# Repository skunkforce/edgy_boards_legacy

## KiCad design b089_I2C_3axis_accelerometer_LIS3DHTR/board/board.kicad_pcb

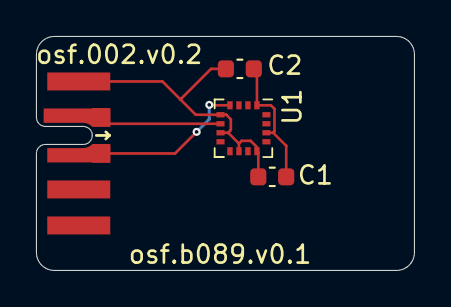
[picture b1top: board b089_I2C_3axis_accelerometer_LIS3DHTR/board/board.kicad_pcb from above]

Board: 2 copper layers, 21.0 x 13.0 mm, 4 parts (0 on the bottom side), 4 nets.

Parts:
C1: 100nF; C_0603_1608Metric
C2: 10uF; C_0603_1608Metric
J1: 001_I2C; on_edge_2x05_device
U1: LIS3DHTR; LGA-16_3x3mm_P0.5mm

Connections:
/sensor/3.3V: C1.2, C2.2, U1.1 (VDD_IO), U1.14 (VDD)
/sensor/SCL: J1.3 (SCL), U1.4 (SCL/SPC)
/sensor/SDA: J1.2 (SDA), U1.6 (SDA/SDI/SDO)
GND: C1.1, C2.1, J1.1 (GND), U1.5 (GND), U1.7 (SDO/SA0), U1.10 (RES), U1.12 (GND)

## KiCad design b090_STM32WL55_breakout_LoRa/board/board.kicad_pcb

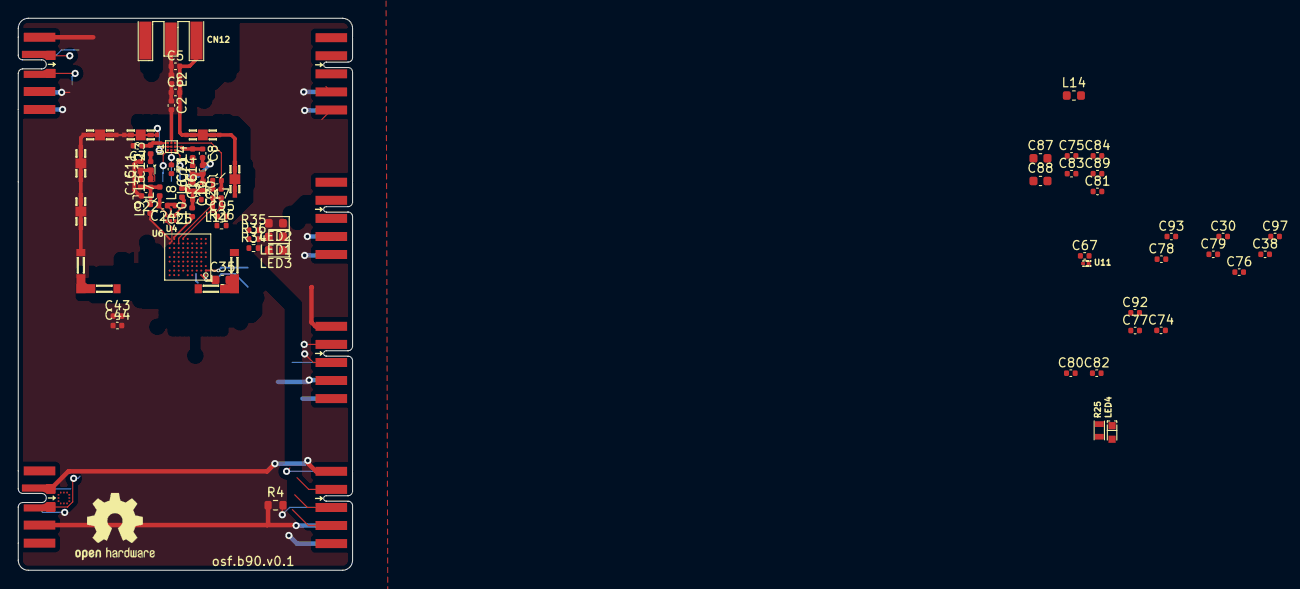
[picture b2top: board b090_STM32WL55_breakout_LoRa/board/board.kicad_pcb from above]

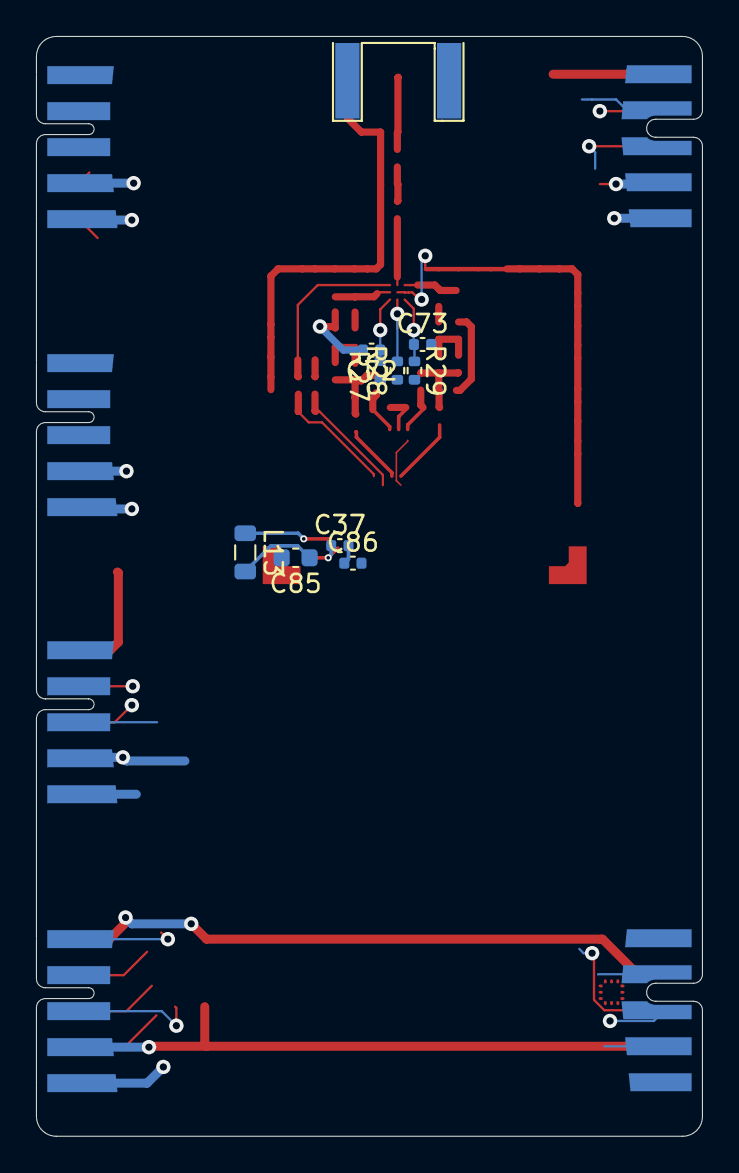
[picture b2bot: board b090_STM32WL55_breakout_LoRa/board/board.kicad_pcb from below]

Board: 4 copper layers, 37.0 x 61.1 mm, 93 parts (9 on the bottom side), 9 nets.

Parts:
C2, C5, C6, C8, C13, C14, C16, C19, C20, C21, C24, C25, C30, C37, C38, C43, C44, C71, C72, C73, C74, C75, C76, C77, C78, C79, C80, C81, C82, C83, C84, C86, C89: C_0402_1005Metric
C7, C11, C12, C15, C17, C22, C92, C93, C95, C97: Capacitor; C_0402_1005Metric
C35, C85, C87, C88: C_0603_1608Metric
C67: C_0402_1005Metric
CN12: CON_SAMTEC_SMA-J-P-X-ST-EM1
J1: DebugEdge_02x05; debug_edge_2x05_device
J2: SPI_2x3; on_edge_2x05_host
J4: UART_2x2; on_edge_2x05_device
J7: I2C_2x2; on_edge_2x05_host
J8: UART_2x2; on_edge_2x05_host
J9: ADC_2x3; on_edge_2x05_host
L2, L4, L8, L9, L10: L_0402_1005Metric
L3, L5, L6, L7, L11: Inductor; L_0402_1005Metric
L13: L_0805_2012Metric
L14: L_0603_1608Metric
LED1, LED2, LED3: D_0603_1608Metric
LED4: LED_0603_VISHAY_VLMS1300-GS08_RED_1A2K_H0P8
LOGO1: Logo_Open_Hardware_Small; OSHW-Logo2_9.8x8mm_SilkScreen
R4: 10k; R_0603_1608Metric
R25: R0603
R26, R27, R28, R29, R34, R35, R36: R_0402_1005Metric
SC1, SC3, SC4, SC5, SC6, SC7: CLIP_HARWIN_S0951-46R
SC8, SC9: Shield-clip_S0981-46R; CLIP_HARWIN_S0951-46R_90
U1: ICC_TSNP-9-3_1P1X1P1_P040
U4: ICC_SOT886_XSON6
U6: ICC_UFBGA73_5X5_P050
U11: ESD_ST0201

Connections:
+3V3: J1.5 (Vref), J2.9 (3.3V), J4.9 (3.3V), J7.9 (3.3V), J8.9 (3.3V), J9.9 (3.3V), R4.1
+5V: J2.10 (5V), J4.10 (5V), J7.10 (5V), J8.10 (5V), J9.10 (5V)
GND: C5.2, C6.2, C7.2, C8.2, C11.2, C14.2, C17.2, C19.2, C21.2, C22.2, C24.1, C25.2, C30.2, C35.2, C37.2, C38.2, C43.2, C44.2, C67.1, C71.2, C72.2, C73.2, C74.2, C75.2, C76.2, C77.2, C78.2, C79.2, C80.2, C81.2, C82.2, C83.2, C84.2, C85.2, C86.2, C87.2, C88.2, C89.2, C92.2, C93.2, C95.2, C97.2, CN12.2 (GND), CN12.3 (GND), CN12.4 (GND), CN12.5 (GND), J1.1 (GND), J2.1 (GND), J4.1 (GND), J7.1 (GND), J8.1 (GND), J9.1 (GND), LED1.1 (K), LED2.1 (K), LED3.1 (K), R26.2, SC1.1, SC3.1, SC4.1, SC5.1, SC6.1, SC7.1, SC8.1, SC9.1, U1.6 (DGND), U1.9 (GND), U4.2 (GND), U6.A1 (VSSSMPS), U6.B7 (VSS), U6.D9 (VSS), U6.E3 (VSS), U6.G5 (VSS), U6.G6 (VSSRF), U6.G7 (VSSRF), U6.G8 (VSSRF), U6.H6 (VSSRF), U11.2
unnamed: C11.1, C12.1, C15.2, L5.2
unnamed: C13.1, C14.1, C16.2, L6.2
unnamed: C13.2, L4.1
unnamed: C71.1, R28.2, U1.8 (V2)
unnamed: C72.1, R27.2, U1.1 (V1)
unnamed: J2.8 (~RESET), R4.2

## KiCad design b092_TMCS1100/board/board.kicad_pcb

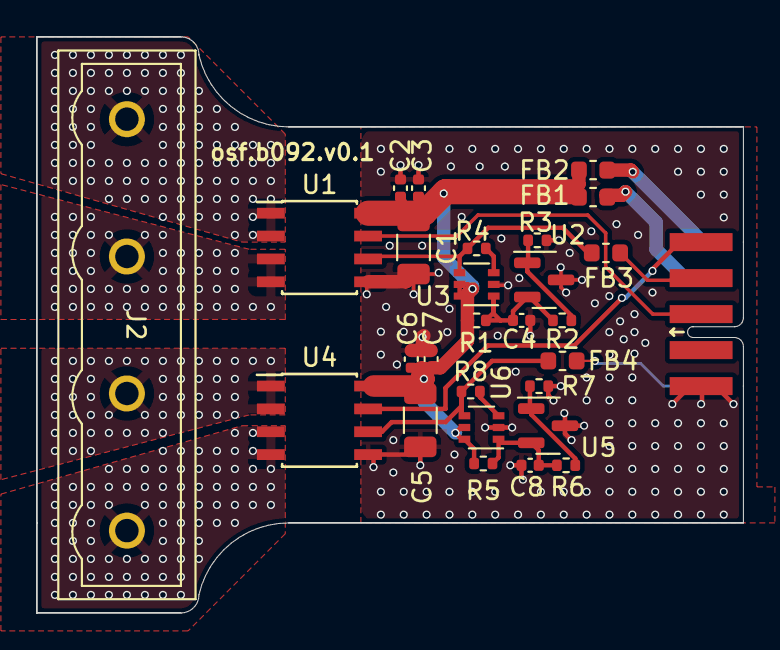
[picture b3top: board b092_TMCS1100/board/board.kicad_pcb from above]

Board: 2 copper layers, 39.2 x 32.0 mm, 28 parts (0 on the bottom side), 20 nets.

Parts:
C1, C5: 10uF; C_1206_3216Metric
C2, C3, C4, C6, C7, C8: 100nF; C_0402_1005Metric
FB1: 200R; L_0603_1608Metric
FB2, FB3, FB4: DNP/200; L_0603_1608Metric
J1: 007_ADC; on_edge_2x05_device
J2: GMSTBVA_2.5_4-G-7.62
R1, R3, R5, R7: 1k; R_0402_1005Metric
R2, R6: 1M; R_0402_1005Metric
R4, R8: 4.7k; R_0402_1005Metric
U1, U4: TMCS1100; SOIC-8_5.4
U2, U5: LM4041-N; SOT-23
U3, U6: LMV601; SOT-363_SC-70-6

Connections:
/VOUT1: J1.3 (ADC0), U1.7 (VOUT)
/VOUT2: J1.5 (ADC2), U4.7 (VOUT)
/VREF: FB3.2, J1.4 (ADC1)
/VREF2: FB4.2, J1.6 (ADC3)
/in+1: J2.1, U1.1 (IN+), U1.2 (IN+)
/in+2: J2.3, U4.1 (IN+), U4.2 (IN+)
/in-1: J2.2, U1.3 (IN-), U1.4 (IN-)
/in-2: J2.4, U4.3 (IN-), U4.4 (IN-)
/tms1100/vref_amp/ADJ: R2.2, R3.1, U2.1 (FB)
/tms1100/vref_amp/VREF_OUT: FB3.1, R4.2, U1.6 (VREF), U3.4
/tms1101/vref_amp/ADJ: R6.2, R7.1, U5.1 (FB)
/tms1101/vref_amp/VREF_OUT: FB4.1, R8.2, U4.6 (VREF), U6.4
GND: C1.2, C2.2, C3.2, C4.2, C5.2, C6.2, C7.2, C8.2, J1.1 (GND), R3.2, R7.2, U1.5 (GND), U2.3 (A), U3.2 (V-), U4.5 (GND), U5.3 (A), U6.2 (V-)
unnamed: C4.1, R1.2, R2.1, U2.2 (K), U3.1 (+)
unnamed: C8.1, R5.2, R6.1, U5.2 (K), U6.1 (+)
unnamed: FB1.2, J1.9 (3.3V)
unnamed: FB2.2, J1.10 (5V)
unnamed: R4.1, U3.3 (-)
unnamed: R8.1, U6.3 (-)
VDDA: C1.1, C2.1, C3.1, C5.1, C6.1, C7.1, FB1.1, FB2.1, R1.1, R5.1, U1.8 (VS), U3.5 (~SHDN), U3.6 (V+), U4.8 (VS), U6.5 (~SHDN), U6.6 (V+)

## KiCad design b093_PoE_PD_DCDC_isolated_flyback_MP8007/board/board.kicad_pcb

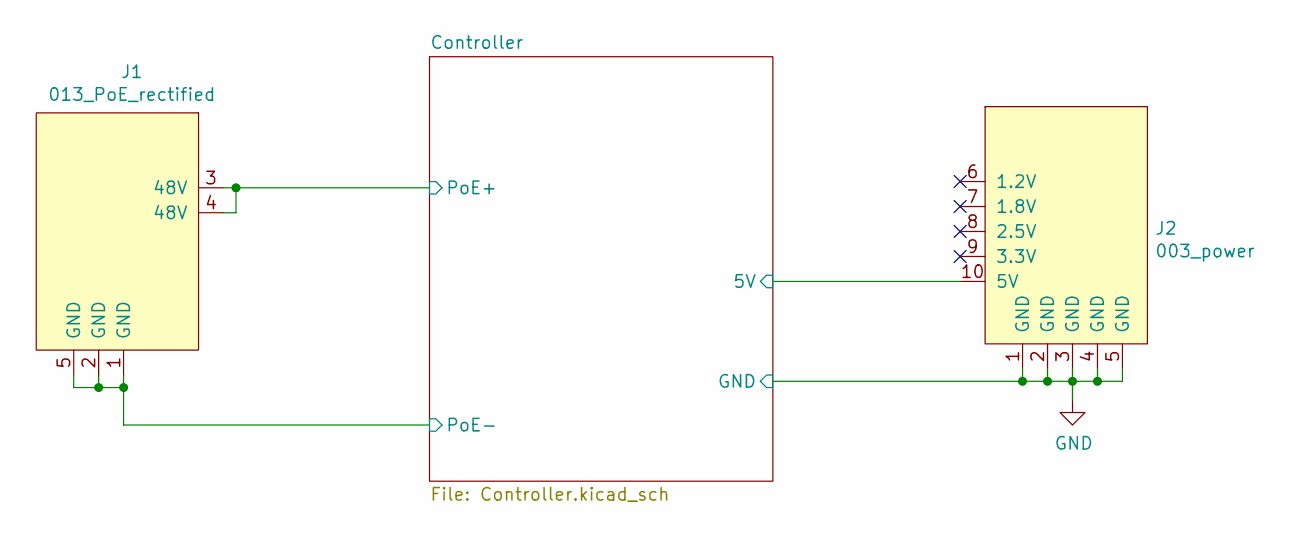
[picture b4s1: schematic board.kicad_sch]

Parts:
J1: 013_PoE_rectified; on_edge_2x05_device
J2: 003_power; on_edge_2x05_host

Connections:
/Controller/5V: J2.10 (5V); also elsewhere on the board
/Controller/PoE+: J1.3 (48V), J1.4 (48V); also elsewhere on the board
/Controller/PoE-: J1.1 (GND), J1.2 (GND), J1.5 (GND); also elsewhere on the board
GND: J2.1 (GND), J2.2 (GND), J2.3 (GND), J2.4 (GND), J2.5 (GND); also elsewhere on the board

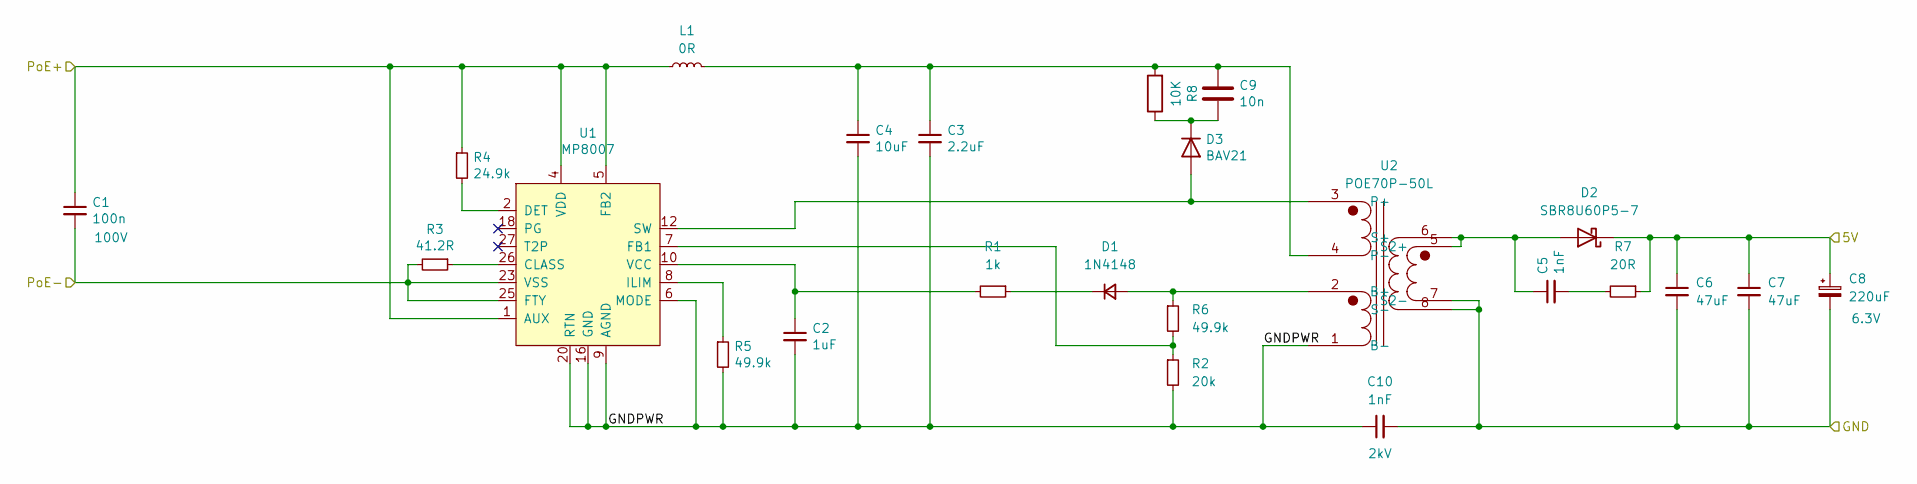
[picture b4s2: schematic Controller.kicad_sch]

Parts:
C1: 100n; C_0603_1608Metric; Voltage 100V
C2: 1uF; C_0603_1608Metric
C3: 2.2uF; C_1210_3225Metric
C4: 10uF; C_1210_3225Metric
C5: 1nF; C_0603_1608Metric
C6, C7: 47uF; C_1210_3225Metric
C8: 220uF; CP_Elec_10x10.5; Voltage 6.3V
C9: 10n; C_0805_2012Metric
C10: 1nF; C_1825_4564Metric; Voltage 2kV
D1: 1N4148; D_SOD-323; DigiKey_PN 1N4148WS_R1_00001
D2: SBR8U60P5-7; D_PowerDI-5
D3: BAV21; D_SOD-323_HandSoldering; DigiKey_PN BAV21WS_R1_00001
L1: 0R; L_1812_4532Metric
R1: 1k; R_0603_1608Metric
R2: 20k; R_0603_1608Metric
R3: 41.2R; R_0603_1608Metric
R4: 24.9k; R_0603_1608Metric
R5, R6: 49.9k; R_0603_1608Metric
R7: 20R; R_0603_1608Metric
R8: 10K; R_1206_3216Metric
U1: MP8007; QFN-28-1EP_4x5mm_P0.5mm_EP2.65x3.65mm_ThermalVias
U2: POE70P-50L; Transformer_Coilcraft_POE70P

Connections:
/Controller/5V: C6.1, C7.1, C8.1, D2.1 (K), R7.1; also elsewhere on the board
/Controller/GNDPWR: C2.2, C3.2, C4.2, C10.1, R2.2, R5.2, U1.6 (MODE), U1.9 (AGND), U1.14 (NC), U1.15 (NC), U1.16 (GND), U1.17, U1.19 (NC), U1.20 (RTN), U1.21, U1.22 (NC), U1.29 (GND), U2.1 (B-)
/Controller/PoE+: C1.1, L1.1, R4.1, U1.1 (AUX), U1.4 (VDD), U1.5 (FB2); also elsewhere on the board
/Controller/PoE-: C1.2, R3.2, U1.23 (VSS), U1.24, U1.25 (FTY); also elsewhere on the board
GND: C6.2, C7.2, C8.2, C10.2, U2.7 (S2-), U2.8 (S-); also elsewhere on the board
unnamed: C2.1, R1.2, U1.10 (VCC)
unnamed: C3.1, C4.1, C9.1, L1.2, R8.2, U2.4 (P-)
unnamed: C5.1, D2.2 (A), U2.5 (S2+), U2.6 (S+)
unnamed: C5.2, R7.2
unnamed: C9.2, D3.1 (K), R8.1
unnamed: D1.1 (K), R1.1
unnamed: D1.2 (A), R6.1, U2.2 (B+)
unnamed: D3.2 (A), U1.12 (SW), U1.13, U2.3 (P+)
unnamed: R2.1, R6.2, U1.7 (FB1)
unnamed: R3.1, U1.26 (CLASS)
unnamed: R4.2, U1.2 (DET)
unnamed: R5.1, U1.8 (ILIM)

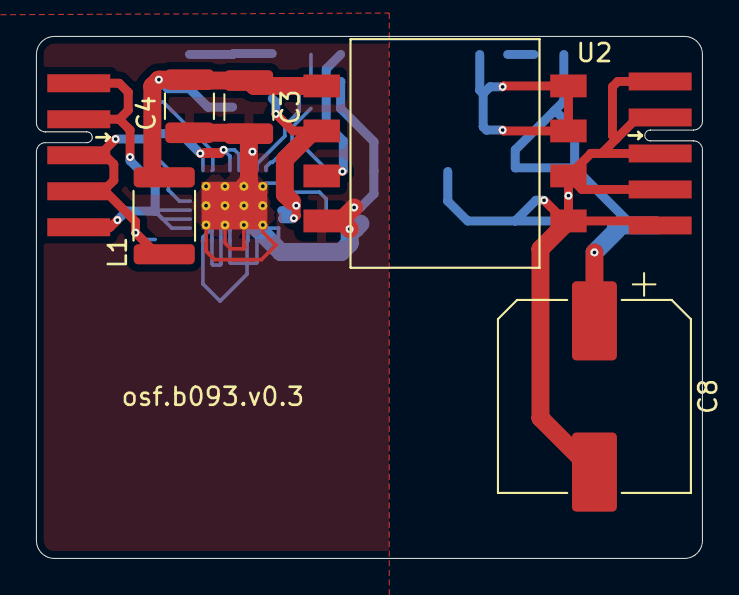
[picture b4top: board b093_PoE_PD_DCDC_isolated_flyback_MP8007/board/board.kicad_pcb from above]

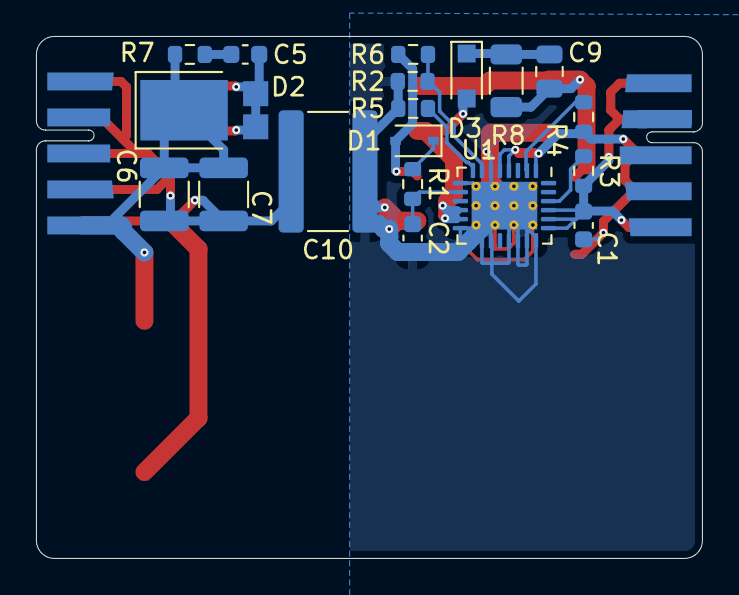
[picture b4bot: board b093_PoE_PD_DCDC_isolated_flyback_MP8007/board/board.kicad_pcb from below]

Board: 2 copper layers, 37.0 x 29.0 mm, 26 parts (19 on the bottom side), 17 nets.

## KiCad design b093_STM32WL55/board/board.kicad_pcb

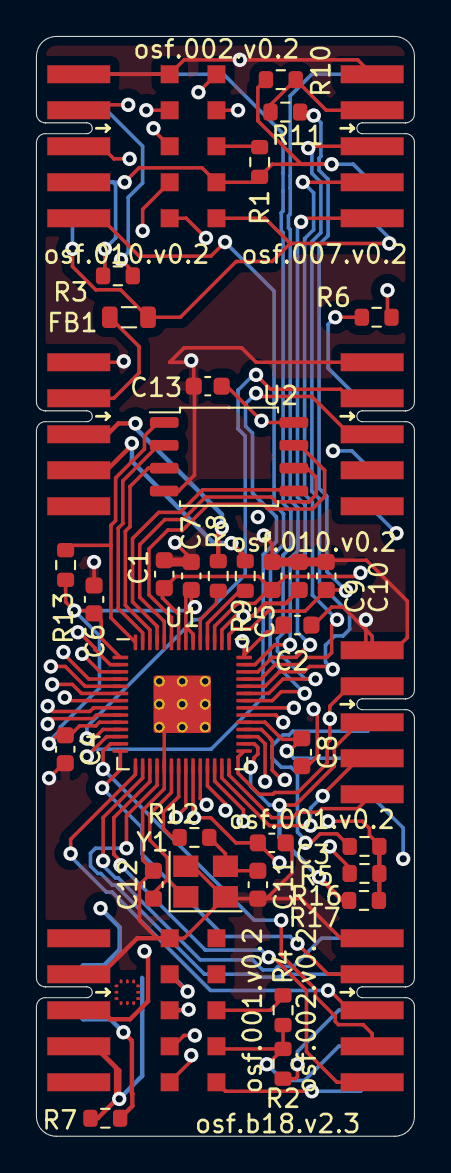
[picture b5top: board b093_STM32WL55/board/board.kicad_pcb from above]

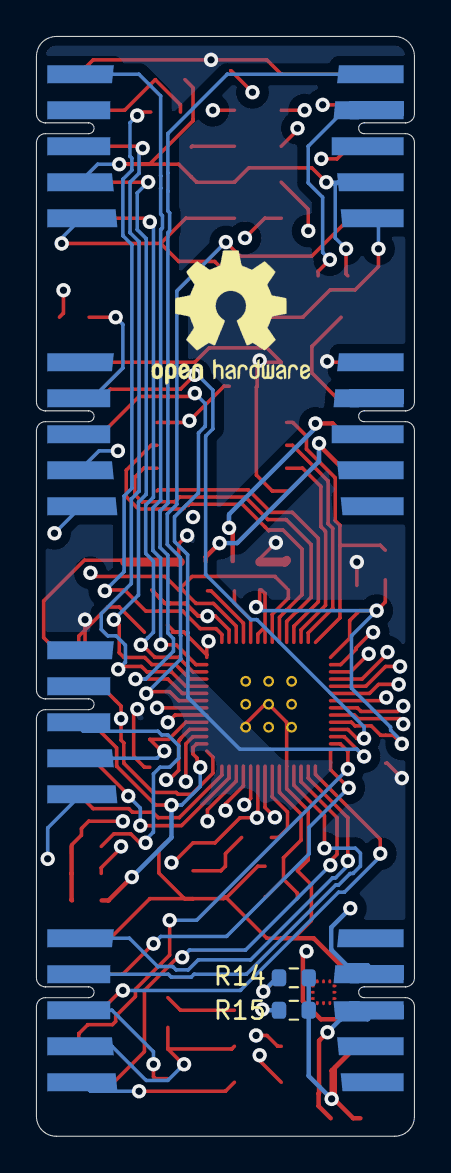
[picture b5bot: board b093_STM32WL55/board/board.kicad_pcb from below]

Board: 4 copper layers, 21.0 x 61.1 mm, 44 parts (3 on the bottom side), 59 nets.

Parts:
C1, C2, C3, C4, C6, C7, C8, C13: 100nF; C_0603_1608Metric
C5, C9, C10: 2.2uF; C_0603_1608Metric
C11, C12: 12pF; C_0603_1608Metric
FB1: Ferrite_Bead_Small; L_0805_2012Metric
J1: SPI_2x3; on_edge_2x05_up_host
J2: I2C_2x2; on_edge_2x05_up_host
J3: UART_2x2; on_edge_2x05_device
J4: SPI_2x3; on_edge_2x05_host
J5: I2C_2x2; on_edge_2x05_host
J6: UART_2x2; on_edge_2x05_host
J7: ADC_2x3; on_edge_2x05_host
J8: DebugEdge_02x05; debug_edge_2x05_device
J9: 008_USB; on_edge_2x05_device
LOGO1: Logo_Open_Hardware_Small; OSHW-Logo2_9.8x8mm_SilkScreen
R1, R2, R3, R4, R5, R6, R7: 10k; R_0603_1608Metric
R8, R9: 27R; R_0603_1608Metric
R10: 200R; R_0603_1608Metric
R11: 1R; R_0603_1608Metric
R12: 1k; R_0603_1608Metric
R13: d.n.p; R_0603_1608Metric
R14, R15, R16, R17: 2k; R_0603_1608Metric
U1: RP2040; RP2040-QFN-56
U2: W25Q128JVS; SOIC-8_5.23x5.23mm_P1.27mm
Y1: 12MhZ; Crystal_SMD_Abracon_ABM8G-4Pin_3.2x2.5mm

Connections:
+3V3: C2.1, C4.1, C6.1, C7.1, C8.1, C9.1, C13.1, J1.9 (3.3V), J2.9 (3.3V), J3.9 (3.3V), J4.9 (3.3V), J5.9 (3.3V), J6.9 (3.3V), J7.9 (3.3V), J8.5 (Vref), R1.1, R2.1, R3.1, R4.1, R5.1, R6.1, R7.1, R10.1, R13.1, R14.1, R15.1, R16.1, R17.1, U1.1 (IOVDD), U1.10 (IOVDD), U1.22 (IOVDD), U1.33 (IOVDD), U1.42 (IOVDD), U1.44 (VREG_IN), U1.48 (USB_VDD), U1.49 (IOVDD), U2.8 (VCC)
+5V: FB1.1, J1.10 (5V), J2.10 (5V), J3.10 (5V), J4.10 (5V), J5.10 (5V), J6.10 (5V), J7.10 (5V)
/ADC0: J7.3 (ADC0), U1.38 (GPIO26_ADC0)
/ADC1: J7.4 (ADC1), U1.39 (GPIO27_ADC1)
/ADC2: J7.5 (ADC2), U1.40 (GPIO28_ADC2)
/ADC3: J7.6 (ADC3), U1.41 (GPIO29_ADC3)
/ADC_VREF: J7.2 (VREF), R10.2, R11.1
/DM: R9.2, U1.46 (USB_DM)
/DP: R8.2, U1.47 (USB_DP)
/GPIO6: J1.5 (INT), U1.8 (GPIO6)
/GPIO7: J1.7 (status), U1.9 (GPIO7)
/GPIO14: J4.5 (INT), U1.17 (GPIO14)
/GPIO15: J4.7 (status), U1.18 (GPIO15)
/GPIO16: J5.4 (CS/EN), U1.27 (GPIO16)
/GPIO17: J5.5 (INT), U1.28 (GPIO17)
/GPIO22: J2.5 (INT), U1.34 (GPIO22)
/GPIO23: J2.4 (CS/EN), U1.35 (GPIO23)
/GPIO24: J3.5 (INT), U1.36 (GPIO24)
/GPIO25: J3.6 (CS/EN), U1.37 (GPIO25)
/I2C0_SCL: J2.3 (SCL), R15.2, U1.32 (GPIO21)
/I2C0_SDA: J2.2 (SDA), R14.2, U1.31 (GPIO20)
/I2C1_SCL: J5.3 (SCL), R17.2, U1.30 (GPIO19)
/I2C1_SDA: J5.2 (SDA), R16.2, U1.29 (GPIO18)
/QPI_SS: R13.2, U1.56 (QSPI_SS), U2.1 (~CS)
/QSPI_CLK: U1.52 (QSPI_SCLK), U2.6 (CLK)
/SPI0_RX: J1.3 (MISO), U1.6 (GPIO4)
/SPI0_SCK: J1.4 (SCLK), U1.4 (GPIO2)
/SPI0_TX: J1.2 (MOSI), U1.5 (GPIO3)
/SPI1_RX: J4.3 (MISO), U1.15 (GPIO12)
/SPI1_SCK: J4.4 (SCLK), U1.13 (GPIO10)
/SPI1_TX: J4.2 (MOSI), U1.14 (GPIO11)
/UART0_RX: J3.2 (TX), U1.3 (GPIO1)
/UART0_TX: J3.3 (RX), U1.2 (GPIO0)
/UART1_RX: J6.3 (RX), U1.12 (GPIO9)
/UART1_TX: J6.2 (TX), U1.11 (GPIO8)
/~SPI0_CS: J1.6 (CS), U1.7 (GPIO5)
/~SPI1_CS: J4.6 (CS), U1.16 (GPIO13)
GND: C1.2, C2.2, C3.2, C4.2, C5.2, C6.2, C7.2, C8.2, C9.2, C10.2, C11.2, C12.2, C13.2, J1.1 (GND), J2.1 (GND), J3.1 (GND), J4.1 (GND), J5.1 (GND), J6.1 (GND), J7.1 (GND), J8.1 (GND), J9.1 (GND), U1.19 (TESTEN), U1.57 (GND), U2.4 (GND), Y1.2, Y1.4
unnamed: C1.1, C3.1, C5.1, U1.23 (DVDD), U1.45 (VREG_VOUT), U1.50 (DVDD)
unnamed: C10.1, R11.2, U1.43 (ADC_AVDD)
unnamed: C11.1, R12.1, Y1.3
unnamed: C12.1, U1.20 (XIN), Y1.1
unnamed: FB1.2, J9.2 (VBUS)
unnamed: J1.8 (~RESET), R1.2
unnamed: J2.8 (~RESET), R4.2
unnamed: J3.7 (~RESET), R3.2
unnamed: J4.8 (~RESET), R2.2
unnamed: J5.8 (~RESET), R5.2
unnamed: J6.7 (~RESET), R6.2
unnamed: J8.2 (SWDIO/TMS), U1.25 (SWD)
unnamed: J8.3 (SWDCLK/TCLK), U1.24 (SWCLK)
unnamed: J8.4 (~RESET), R7.2, U1.26 (RUN)
unnamed: J9.3 (DP), R8.1
unnamed: J9.4 (DM), R9.1
unnamed: R12.2, U1.21 (XOUT)
unnamed: U1.51 (QSPI_SD3), U2.7 (IO3)
unnamed: U1.53 (QSPI_SD0), U2.5 (DI(IO0))
unnamed: U1.54 (QSPI_SD2), U2.3 (IO2)
unnamed: U1.55 (QSPI_SD1), U2.2 (DO(IO1))

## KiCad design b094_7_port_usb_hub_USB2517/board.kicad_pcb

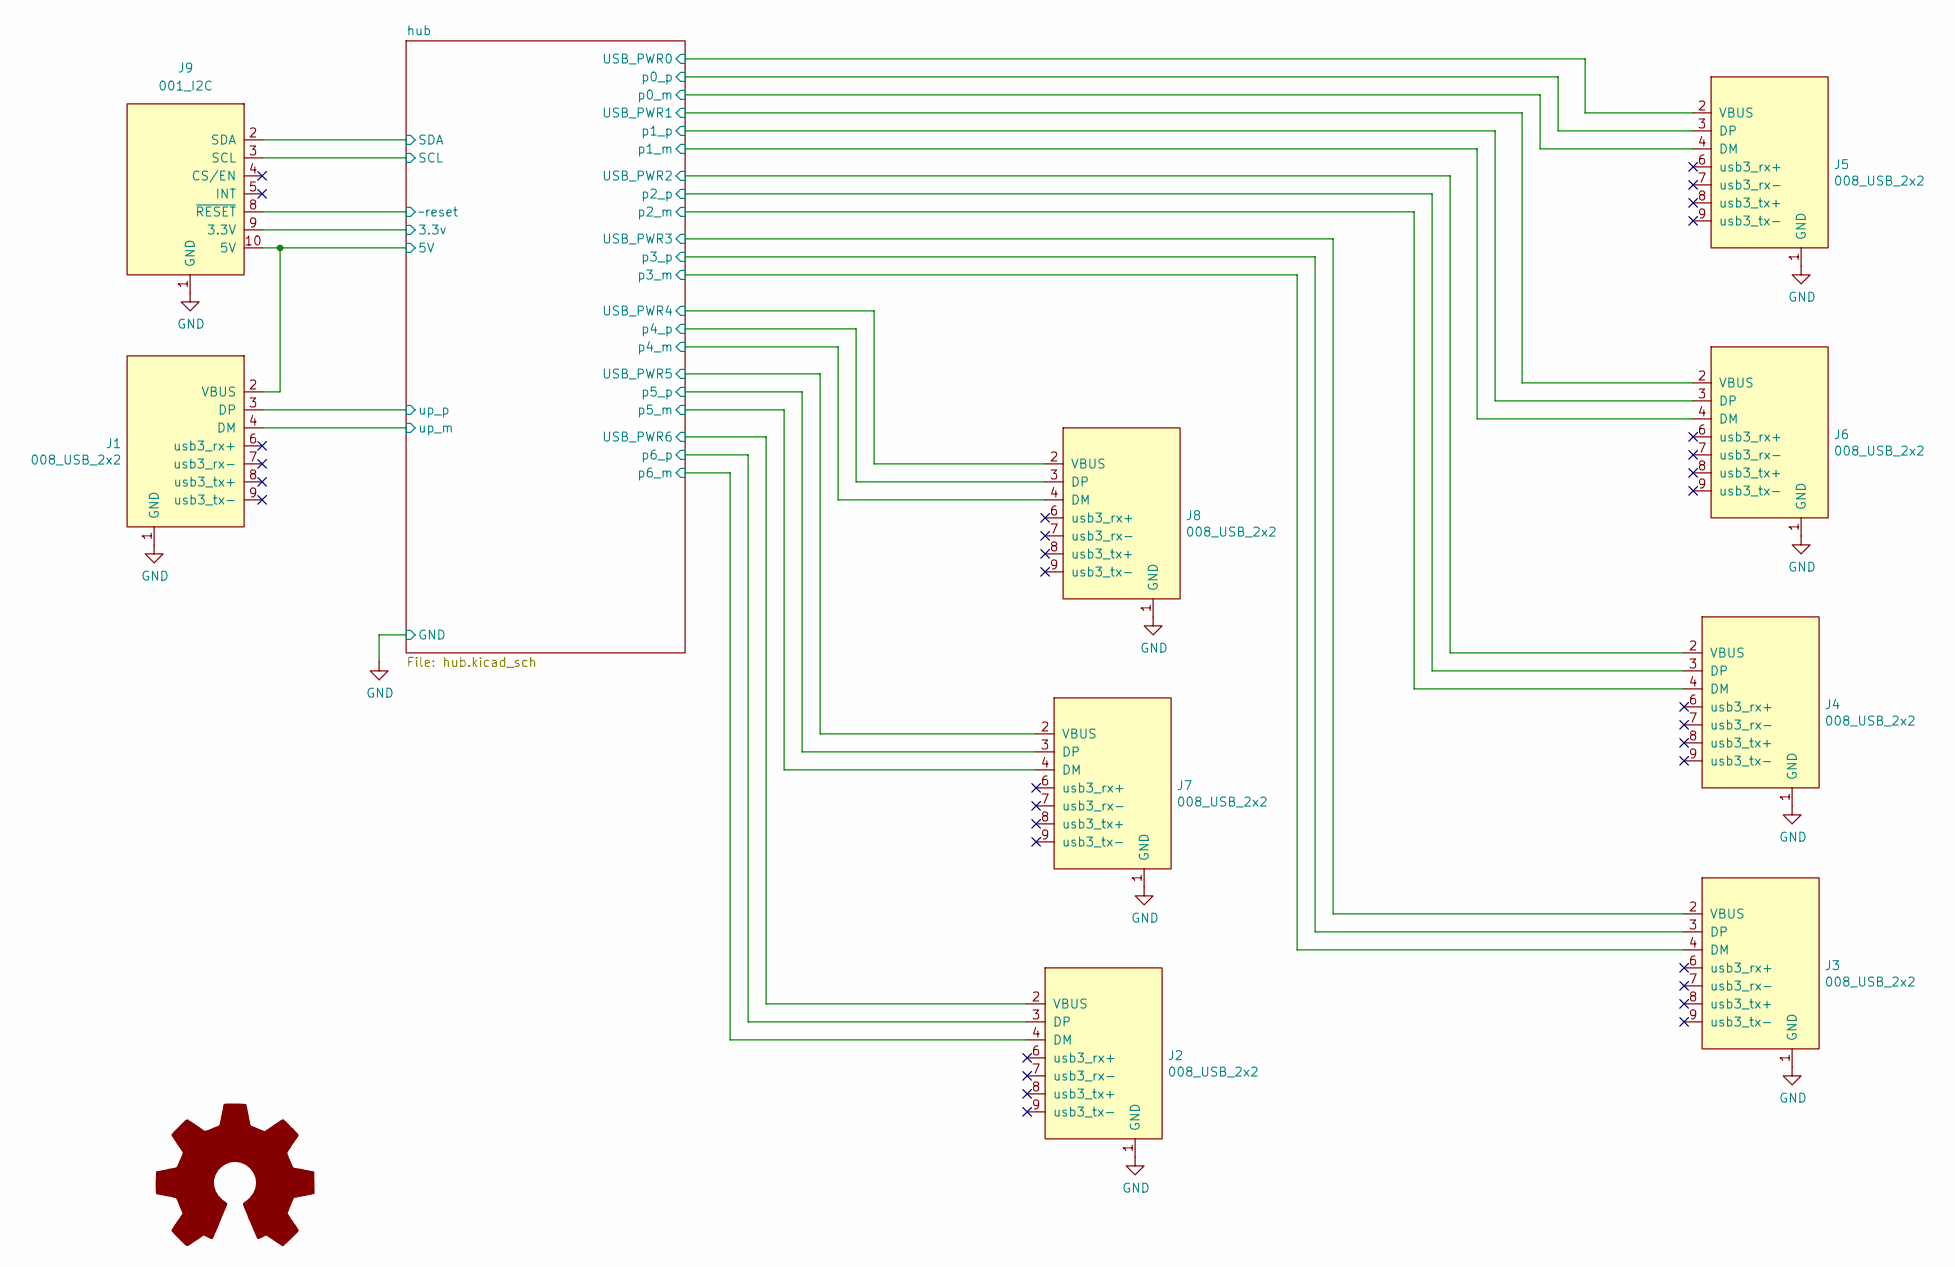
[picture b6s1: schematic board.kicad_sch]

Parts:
J1: 008_USB_2x2; on_edge_2x05_device
J2, J3, J4, J5, J6, J7, J8: 008_USB_2x2; on_edge_2x05_host
J9: 001_I2C; on_edge_2x05_device
l1: Logo_Open_Hardware_Large; OSHW-Logo2_7.3x6mm_SilkScreen

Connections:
/hub/3.3v: J9.9 (3.3V); also elsewhere on the board
/hub/5V: J1.2 (VBUS), J9.10 (5V); also elsewhere on the board
/hub/SCL: J9.3 (SCL); also elsewhere on the board
/hub/SDA: J9.2 (SDA); also elsewhere on the board
/hub/USB_PWR0: J5.2 (VBUS); also elsewhere on the board
/hub/USB_PWR1: J6.2 (VBUS); also elsewhere on the board
/hub/USB_PWR2: J4.2 (VBUS); also elsewhere on the board
/hub/USB_PWR3: J3.2 (VBUS); also elsewhere on the board
/hub/USB_PWR4: J8.2 (VBUS); also elsewhere on the board
/hub/USB_PWR5: J7.2 (VBUS); also elsewhere on the board
/hub/USB_PWR6: J2.2 (VBUS); also elsewhere on the board
/hub/p0_m: J5.4 (DM); also elsewhere on the board
/hub/p0_p: J5.3 (DP); also elsewhere on the board
/hub/p1_m: J6.4 (DM); also elsewhere on the board
/hub/p1_p: J6.3 (DP); also elsewhere on the board
/hub/p2_m: J4.4 (DM); also elsewhere on the board
/hub/p2_p: J4.3 (DP); also elsewhere on the board
/hub/p3_m: J3.4 (DM); also elsewhere on the board
/hub/p3_p: J3.3 (DP); also elsewhere on the board
/hub/p4_m: J8.4 (DM); also elsewhere on the board
/hub/p4_p: J8.3 (DP); also elsewhere on the board
/hub/p5_m: J7.4 (DM); also elsewhere on the board
/hub/p5_p: J7.3 (DP); also elsewhere on the board
/hub/p6_m: J2.4 (DM); also elsewhere on the board
/hub/p6_p: J2.3 (DP); also elsewhere on the board
/hub/up_m: J1.4 (DM); also elsewhere on the board
/hub/up_p: J1.3 (DP); also elsewhere on the board
/hub/~reset: J9.8 (~RESET); also elsewhere on the board
GND: J1.1 (GND), J2.1 (GND), J3.1 (GND), J4.1 (GND), J5.1 (GND), J6.1 (GND), J7.1 (GND), J8.1 (GND), J9.1 (GND); also elsewhere on the board

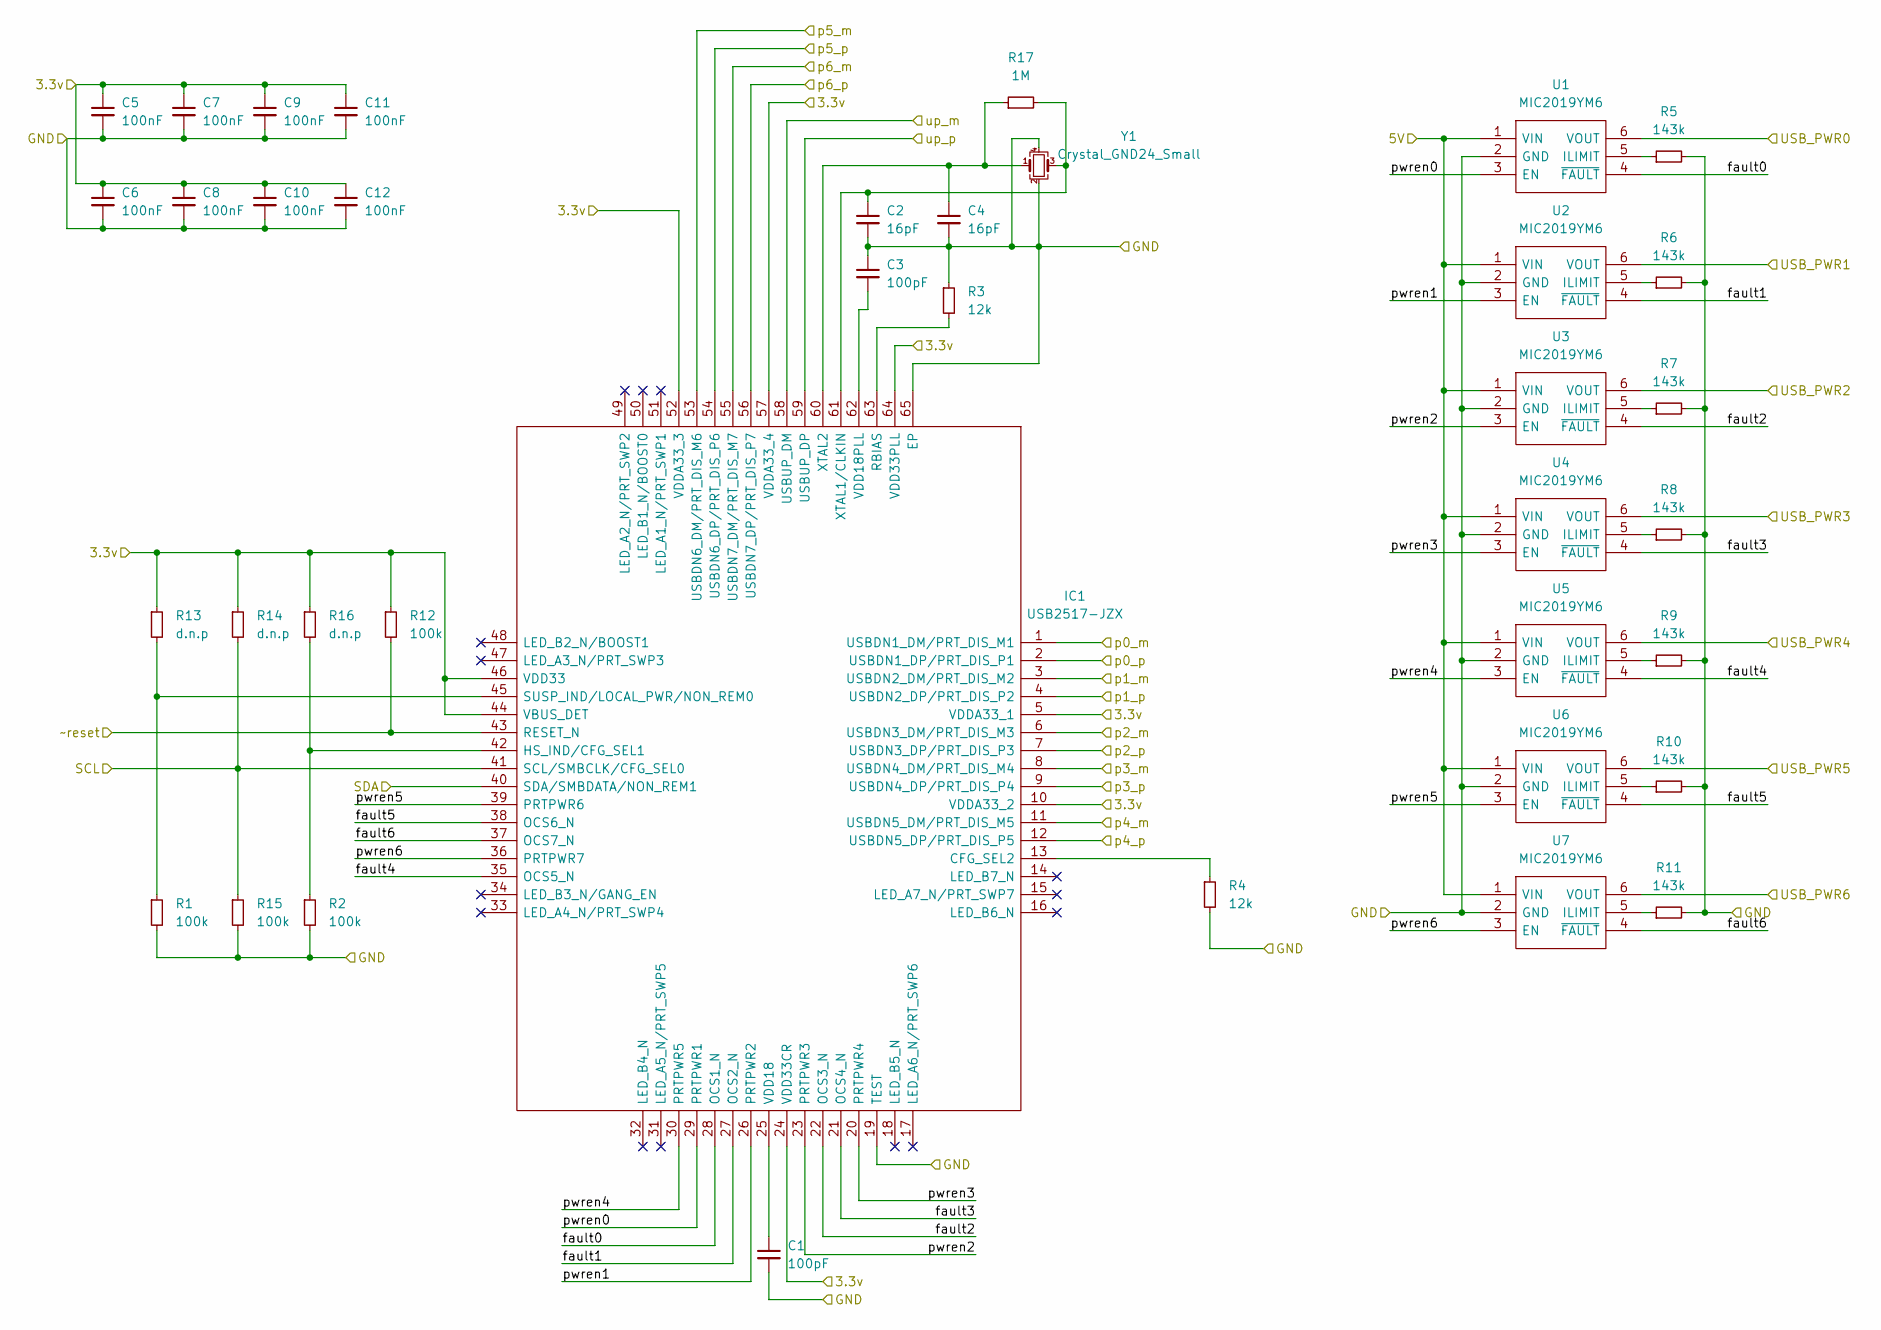
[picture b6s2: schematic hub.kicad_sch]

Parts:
C1, C3: 100pF; C_0402_1005Metric
C2, C4: 16pF; C_0402_1005Metric
C5, C6, C7, C8, C9, C10, C11, C12: 100nF; C_0402_1005Metric
IC1: USB2517-JZX; QFN-64-1EP_9x9mm_P0.5mm_EP4.7x4.7mm; Mouser Part Number 886-USB2517-JZX
R1, R2, R12, R15: 100k; C_0603_1608Metric
R3, R4: 12k; C_0603_1608Metric
R5, R6, R7, R8, R9, R10, R11: 143k; C_0603_1608Metric
R13, R14, R16: d.n.p; C_0603_1608Metric
R17: 1M; C_0603_1608Metric
U1, U2, U3, U4, U5, U6, U7: MIC2019YM6; TSOP-6_1.65x3.05mm_P0.95mm; Mouser Part Number 998-MIC2019YM6TR
Y1: Crystal_GND24_Small; Oscillator_SMD_Abracon_ASE-4Pin_3.2x2.5mm_HandSoldering

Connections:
/hub/3.3v: C5.1, C6.1, C7.1, C8.1, C9.1, C10.1, C11.1, C12.1, IC1.5 (VDDA33_1), IC1.10 (VDDA33_2), IC1.24 (VDD33CR), IC1.44 (VBUS_DET), IC1.46 (VDD33), IC1.52 (VDDA33_3), IC1.57 (VDDA33_4), IC1.64 (VDD33PLL), R12.1, R13.1, R14.1, R16.1; also elsewhere on the board
/hub/5V: U1.1 (VIN), U2.1 (VIN), U3.1 (VIN), U4.1 (VIN), U5.1 (VIN), U6.1 (VIN), U7.1 (VIN); also elsewhere on the board
/hub/SCL: IC1.41 (SCL/SMBCLK/CFG_SEL0), R14.2, R15.1; also elsewhere on the board
/hub/SDA: IC1.40 (SDA/SMBDATA/NON_REM1); also elsewhere on the board
/hub/USB_PWR0: U1.6 (VOUT); also elsewhere on the board
/hub/USB_PWR1: U2.6 (VOUT); also elsewhere on the board
/hub/USB_PWR2: U3.6 (VOUT); also elsewhere on the board
/hub/USB_PWR3: U4.6 (VOUT); also elsewhere on the board
/hub/USB_PWR4: U5.6 (VOUT); also elsewhere on the board
/hub/USB_PWR5: U6.6 (VOUT); also elsewhere on the board
/hub/USB_PWR6: U7.6 (VOUT); also elsewhere on the board
/hub/fault0: IC1.28 (OCS1_N), U1.4 (~FAULT)
/hub/fault1: IC1.27 (OCS2_N), U2.4 (~FAULT)
/hub/fault2: IC1.22 (OCS3_N), U3.4 (~FAULT)
/hub/fault3: IC1.21 (OCS4_N), U4.4 (~FAULT)
/hub/fault4: IC1.35 (OCS5_N), U5.4 (~FAULT)
/hub/fault5: IC1.38 (OCS6_N), U6.4 (~FAULT)
/hub/fault6: IC1.37 (OCS7_N), U7.4 (~FAULT)
/hub/p0_m: IC1.1 (USBDN1_DM/PRT_DIS_M1); also elsewhere on the board
/hub/p0_p: IC1.2 (USBDN1_DP/PRT_DIS_P1); also elsewhere on the board
/hub/p1_m: IC1.3 (USBDN2_DM/PRT_DIS_M2); also elsewhere on the board
/hub/p1_p: IC1.4 (USBDN2_DP/PRT_DIS_P2); also elsewhere on the board
/hub/p2_m: IC1.6 (USBDN3_DM/PRT_DIS_M3); also elsewhere on the board
/hub/p2_p: IC1.7 (USBDN3_DP/PRT_DIS_P3); also elsewhere on the board
/hub/p3_m: IC1.8 (USBDN4_DM/PRT_DIS_M4); also elsewhere on the board
/hub/p3_p: IC1.9 (USBDN4_DP/PRT_DIS_P4); also elsewhere on the board
/hub/p4_m: IC1.11 (USBDN5_DM/PRT_DIS_M5); also elsewhere on the board
/hub/p4_p: IC1.12 (USBDN5_DP/PRT_DIS_P5); also elsewhere on the board
/hub/p5_m: IC1.53 (USBDN6_DM/PRT_DIS_M6); also elsewhere on the board
/hub/p5_p: IC1.54 (USBDN6_DP/PRT_DIS_P6); also elsewhere on the board
/hub/p6_m: IC1.55 (USBDN7_DM/PRT_DIS_M7); also elsewhere on the board
/hub/p6_p: IC1.56 (USBDN7_DP/PRT_DIS_P7); also elsewhere on the board
/hub/pwren0: IC1.29 (PRTPWR1), U1.3 (EN)
/hub/pwren1: IC1.26 (PRTPWR2), U2.3 (EN)
/hub/pwren2: IC1.23 (PRTPWR3), U3.3 (EN)
/hub/pwren3: IC1.20 (PRTPWR4), U4.3 (EN)
/hub/pwren4: IC1.30 (PRTPWR5), U5.3 (EN)
/hub/pwren5: IC1.39 (PRTPWR6), U6.3 (EN)
/hub/pwren6: IC1.36 (PRTPWR7), U7.3 (EN)
/hub/up_m: IC1.58 (USBUP_DM); also elsewhere on the board
/hub/up_p: IC1.59 (USBUP_DP); also elsewhere on the board
/hub/~reset: IC1.43 (RESET_N), R12.2; also elsewhere on the board
GND: C1.2, C2.2, C3.1, C4.2, C5.2, C6.2, C7.2, C8.2, C9.2, C10.2, C11.2, C12.2, IC1.19 (TEST), IC1.65 (EP), R1.2, R2.2, R3.1, R4.2, R5.2, R6.2, R7.2, R8.2, R9.2, R10.2, R11.2, R15.2, U1.2 (GND), U2.2 (GND), U3.2 (GND), U4.2 (GND), U5.2 (GND), U6.2 (GND), U7.2 (GND), Y1.2, Y1.4; also elsewhere on the board
unnamed: C1.1, IC1.25 (VDD18)
unnamed: C2.1, IC1.61 (XTAL1/CLKIN), R17.2, Y1.3
unnamed: C3.2, IC1.62 (VDD18PLL)
unnamed: C4.1, IC1.60 (XTAL2), R17.1, Y1.1
unnamed: IC1.13 (CFG_SEL2), R4.1
unnamed: IC1.42 (HS_IND/CFG_SEL1), R2.1, R16.2
unnamed: IC1.45 (SUSP_IND/LOCAL_PWR/NON_REM0), R1.1, R13.2
unnamed: IC1.63 (RBIAS), R3.2
unnamed: R5.1, U1.5 (ILIMIT)
unnamed: R6.1, U2.5 (ILIMIT)
unnamed: R7.1, U3.5 (ILIMIT)
unnamed: R8.1, U4.5 (ILIMIT)
unnamed: R9.1, U5.5 (ILIMIT)
unnamed: R10.1, U6.5 (ILIMIT)
unnamed: R11.1, U7.5 (ILIMIT)

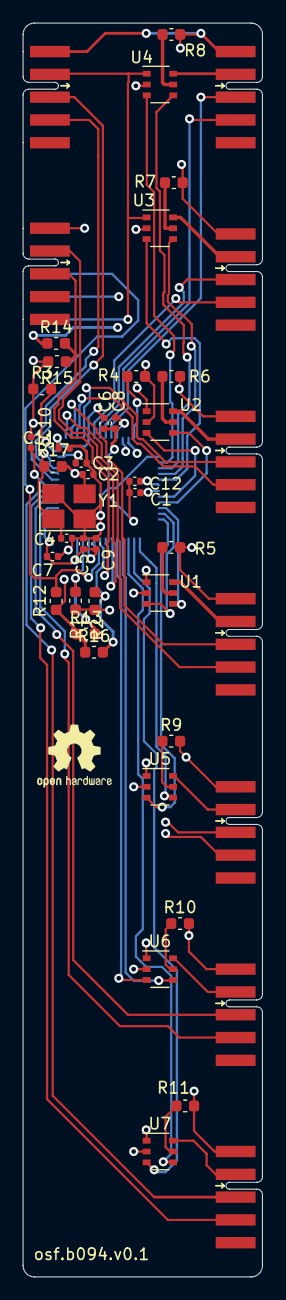
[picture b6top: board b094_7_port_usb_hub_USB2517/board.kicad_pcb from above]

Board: 4 copper layers, 21.0 x 110.0 mm, 48 parts (1 on the bottom side), 58 nets.

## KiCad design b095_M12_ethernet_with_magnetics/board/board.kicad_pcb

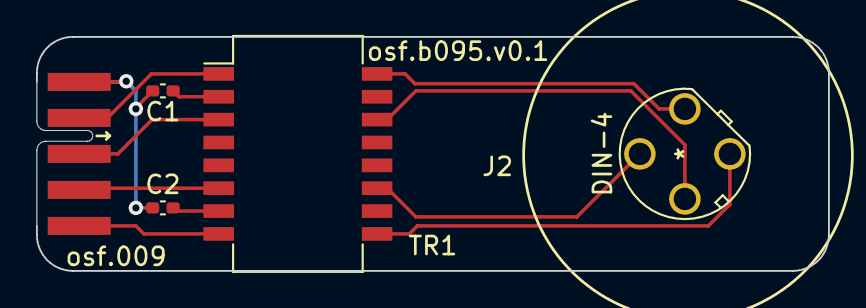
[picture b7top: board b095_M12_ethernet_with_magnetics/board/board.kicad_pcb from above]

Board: 2 copper layers, 44.0 x 13.0 mm, 5 parts (0 on the bottom side), 11 nets.

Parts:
C1, C2: 100nF; C_0402_1005Metric_Pad0.74x0.62mm_HandSolder
J1: 009_1000BASE-T; on_edge_2x05_device
J2: DIN-4; M12D
TR1: 749013011A

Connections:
/magnetics/RX+: J1.4 (TD2+), TR1.6 (RD+)
/magnetics/RX-: J1.5 (TD2-), TR1.8 (RD-)
/magnetics/RXD+: J2.4, TR1.11 (RX+)
/magnetics/RXD-: J2.2, TR1.9 (RX-)
/magnetics/TX+: J1.2 (TD1+), TR1.1 (TD+)
/magnetics/TX-: J1.3 (TD1-), TR1.3 (TD-)
/magnetics/TXD+: J2.1, TR1.16 (TX+)
/magnetics/TXD-: J2.3, TR1.14 (TX-)
GND: C1.2, C2.2, J1.1 (GND), J1.6 (GND)
unnamed: C1.1, TR1.2 (C_TD)
unnamed: C2.1, TR1.7 (C_RD)
